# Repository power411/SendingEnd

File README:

Hello World!  This contains our documentation of sending module for an IR transmission device.

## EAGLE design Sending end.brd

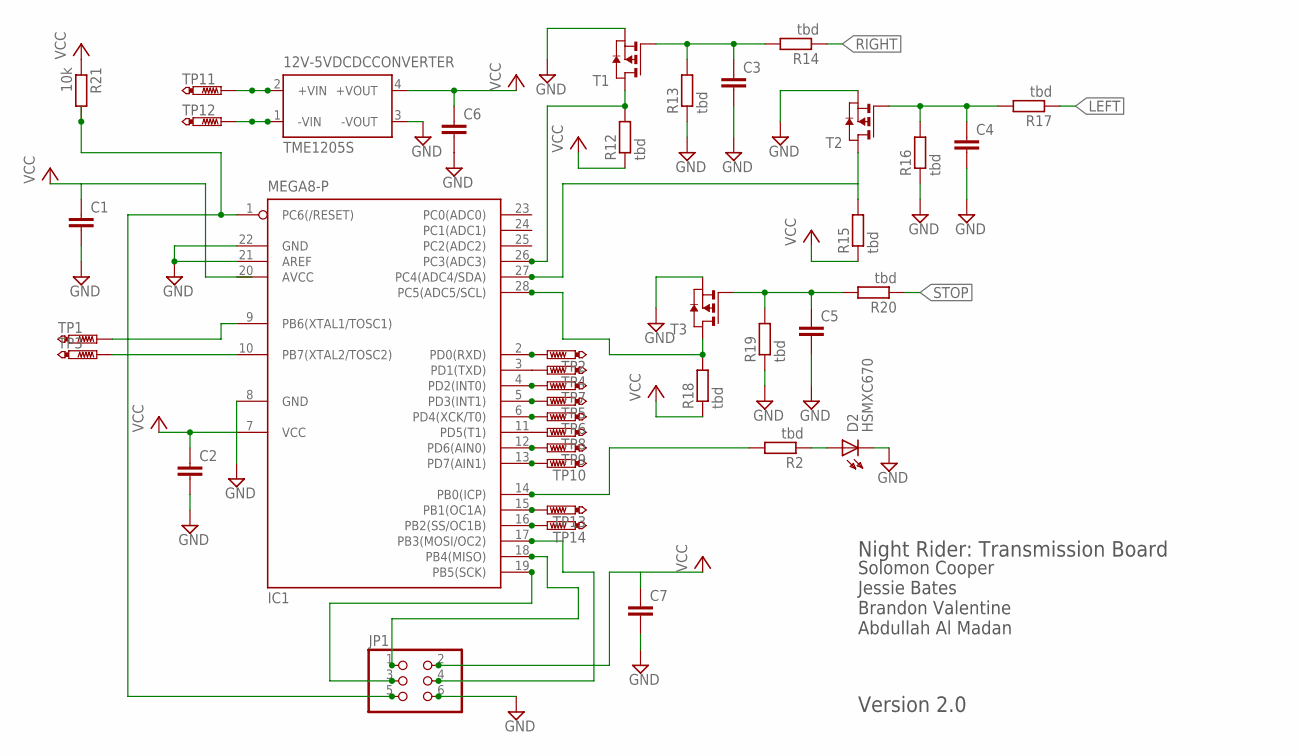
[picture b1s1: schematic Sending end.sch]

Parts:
12V-5VDCDCCONVERTER: TME1205S; TME; MPN TME 1205S
C1, C2, C3, C4, C5, C6, C7: C-EUC0805; C0805
D2: HSMXC670
IC1: MEGA8-P; DIL28-3
JP1: PINHD-2X3; 2X03
R2, R12, R13, R14, R15, R16, R17, R18, R19, R20: tbd; M0805
R21: 10k; M0805
T1, T2, T3: PMOSSOT23; SOT-23
TP1, TP2, TP3, TP4, TP5, TP6, TP7, TP8, TP9, TP10, TP11, TP12, TP13, TP14: PTR1PAD1-20; P1-20

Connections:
AVCC: IC1.20 (AVCC)
GND: 12V-5VDCDCCONVERTER.3 (-VOUT), C2.2, C3.2, C4.2, C5.2, C7.2, D2.K (C), IC1.8 (GND), IC1.21 (AREF), IC1.22 (GND), JP1.6, R13.1, R16.1, R19.1, T1.2 (S), T2.2 (S), T3.2 (S)
LEFT: R17.1
unnamed: IC1.5 (PD3(INT1)), TP5.TP
unnamed: D2.A, R2.1
unnamed: IC1.1 (PC6(/RESET)), JP1.5, R21.2
unnamed: C3.1, R13.2, R14.2, T1.3 (G)
unnamed: IC1.9 (PB6(XTAL1/TOSC1)), TP1.TP
unnamed: IC1.28 (PC5(ADC5/SCL)), R18.2, T3.1 (D)
unnamed: IC1.3 (PD1(TXD)), TP4.TP
unnamed: IC1.4 (PD2(INT0)), TP7.TP
unnamed: IC1.6 (PD4(XCK/T0)), TP6.TP
unnamed: IC1.12 (PD6(AIN0)), TP9.TP
unnamed: IC1.13 (PD7(AIN1)), TP10.TP
unnamed: IC1.14 (PB0(ICP)), R2.2
unnamed: IC1.15 (PB1(OC1A)), TP13.TP
unnamed: IC1.16 (PB2(SS/OC1B)), TP14.TP
unnamed: IC1.17 (PB3(MOSI/OC2)), JP1.4
unnamed: IC1.18 (PB4(MISO)), JP1.1
unnamed: IC1.19 (PB5(SCK)), JP1.3
unnamed: 12V-5VDCDCCONVERTER.2 (+VIN), TP11.TP
unnamed: 12V-5VDCDCCONVERTER.1 (-VIN), TP12.TP
unnamed: C1.2, C6.2
unnamed: C4.1, R16.2, R17.2, T2.3 (G)
unnamed: R15.2, T2.1 (D)
unnamed: C5.1, R19.2, R20.2, T3.3 (G)
unnamed: IC1.10 (PB7(XTAL2/TOSC2)), TP3.TP
unnamed: IC1.11 (PD5(T1)), TP8.TP
unnamed: IC1.26 (PC3(ADC3)), R12.2, T1.1 (D)
RIGHT: R14.1
STOP: R20.1
VCC: 12V-5VDCDCCONVERTER.4 (+VOUT), C1.1, C6.1, IC1.7 (VCC), JP1.2, R12.1, R15.1, R18.1, R21.1
VCC1: C7.1

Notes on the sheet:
Night Rider: Transmission Board
Solomon Cooper Jessie Bates Brandon Valentine Abdullah Al Madan
Version 2.0

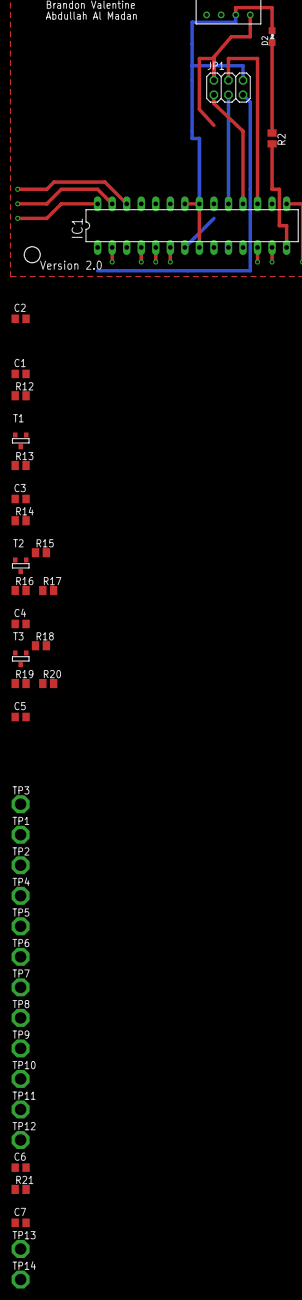
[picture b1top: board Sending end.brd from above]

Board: 2 copper layers, 39 parts (0 on the bottom side), 28 nets.

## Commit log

2012-11-03 First Commit
    This first commit contains the sending end schematic of our IR
    transmission device.
2012-11-03 readme updated
2012-11-04 polished schematic
2012-11-06 initial bored layout
2012-11-06 no error initial layout
2012-11-06 The Sending End layout before going through the checklist
2012-11-06 Sending End Layout before meeting with Greenberg
2012-11-06 sending end echematic version 3.0. need more work on the DCDC converter
2012-11-09 the sending end schematic Version 4.0 it has the following modifications: DCtoDCconverter connected as desired; the diode for transmission has an NMOS transistor to amplify the current
